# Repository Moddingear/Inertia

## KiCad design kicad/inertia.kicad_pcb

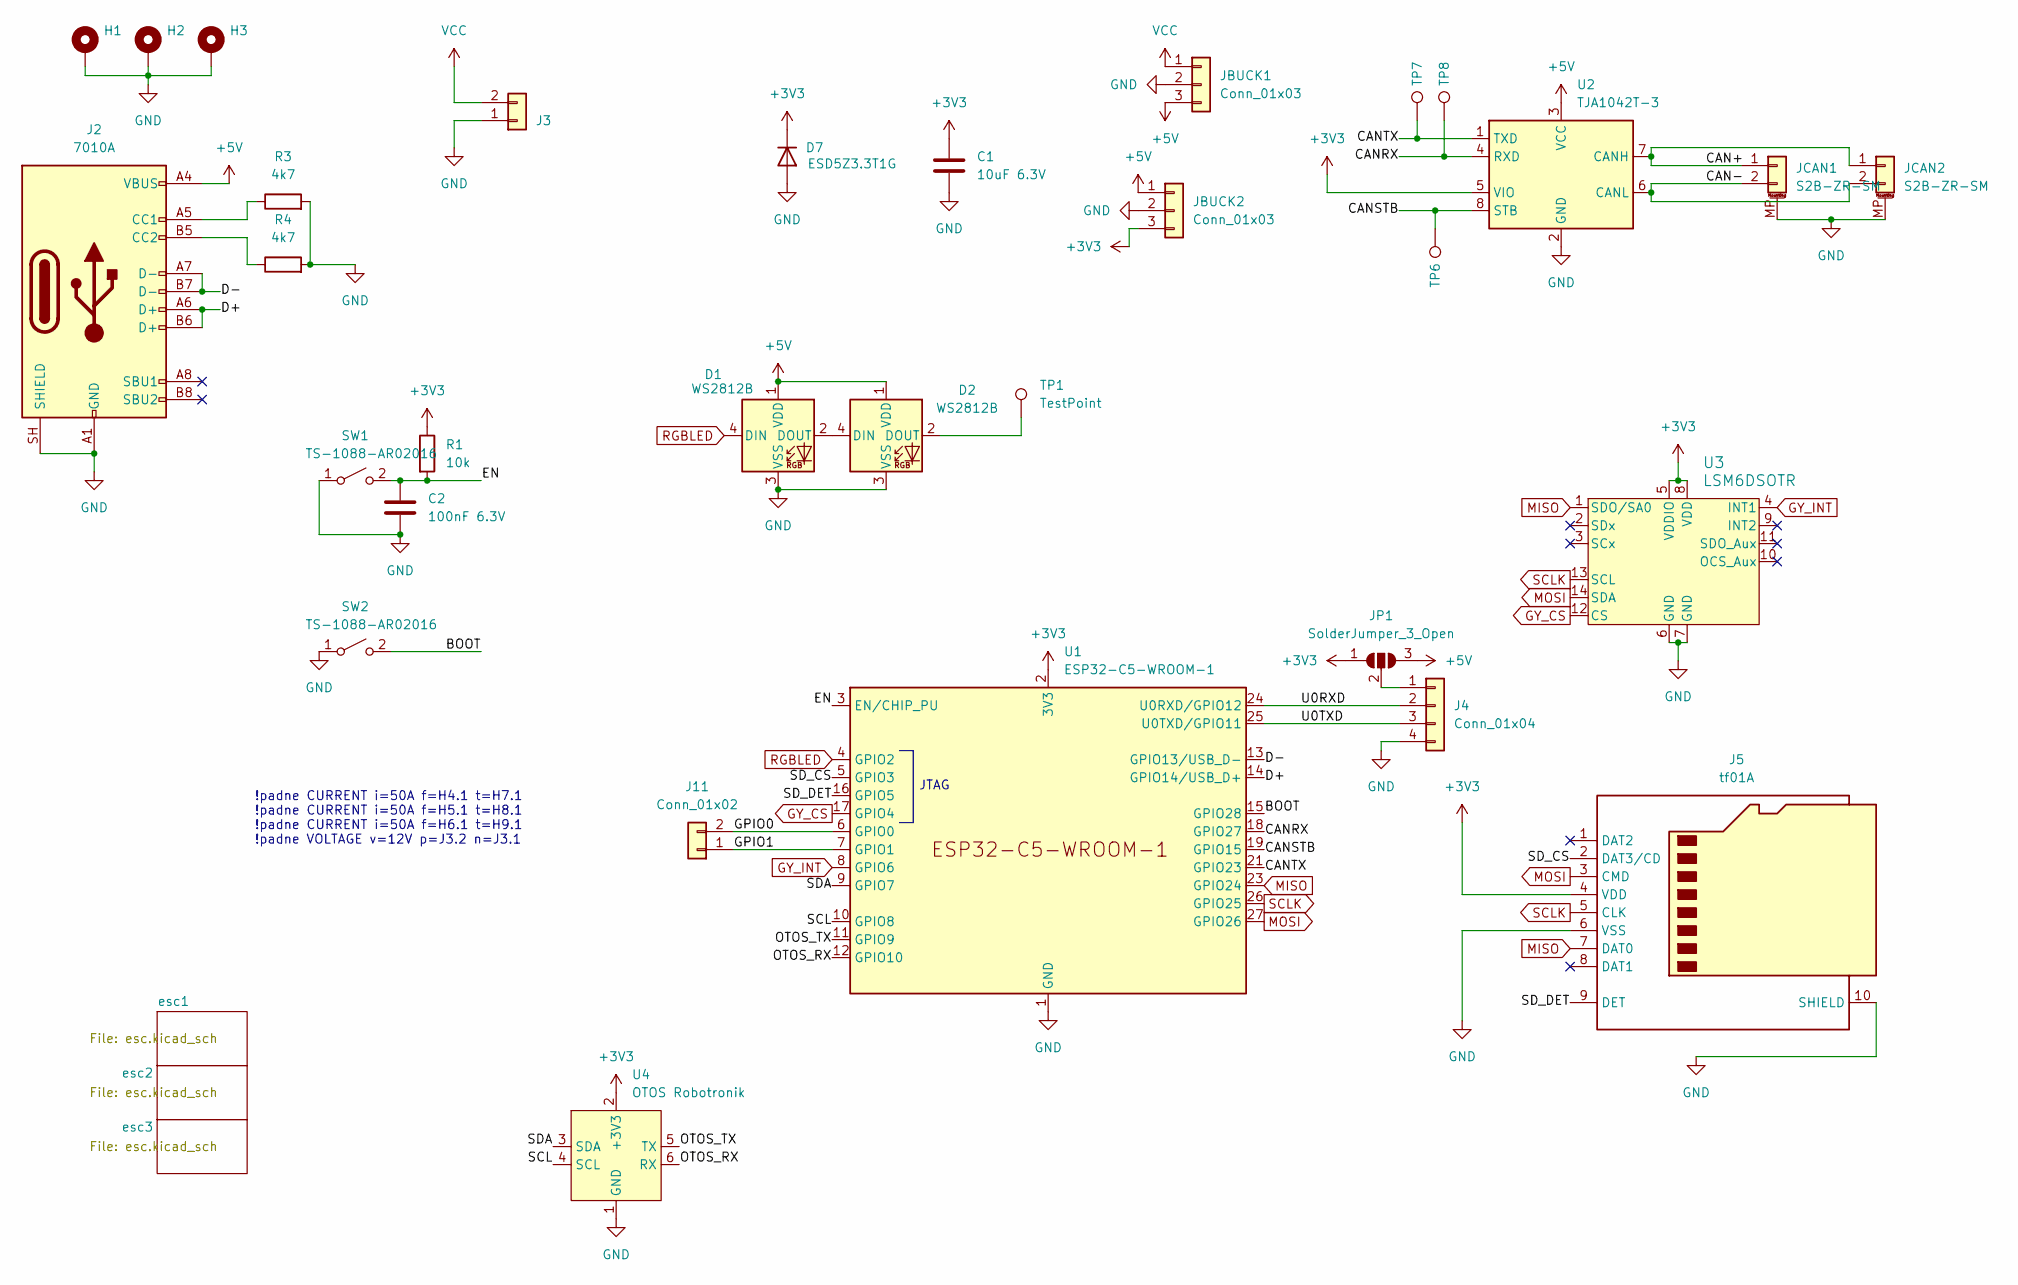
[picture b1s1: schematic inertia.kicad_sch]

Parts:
C1: 10uF 6.3V; C_0805_2012Metric_Pad1.18x1.45mm_HandSolder
C2: 100nF 6.3V; C_0805_2012Metric
D1, D2: WS2812B; LED_WS2812B_PLCC4_5.0x5.0mm_P3.2mm
D7: ESD5Z3.3T1G; D_SOD-523
H1, H2, H3: MountingHole_Pad; MountingHole_3.2mm_M3_ISO7380_Pad
J2: 7010A; USB_C_Receptacle_G-Switch_GT-USB-7010ASV
J3: Conn_01x02; AMASS_XT60-F_1x02_P7.20mm_Vertical
J4: Conn_01x04; JST_XH_B4B-XH-AM_1x04_P2.50mm_Vertical
J5: tf01A; TF-01A
J11: Conn_01x02; JST_XH_B2B-XH-A_1x02_P2.50mm_Vertical
JBUCK1, JBUCK2: Conn_01x03; PinHeader_1x03_P2.54mm_Vertical
JCAN1, JCAN2: S2B-ZR-SM; S2B-ZR-SMxA
JP1: SolderJumper_3_Open; SolderJumper-3_P1.3mm_Open_RoundedPad1.0x1.5mm
R1: 10k; R_0603_1608Metric_Pad0.98x0.95mm_HandSolder
R3, R4: 4k7; R_0603_1608Metric_Pad0.98x0.95mm_HandSolder
SW1, SW2: TS-1088-AR02016; SW_SPST_TS-1088-xR020
TP1: TestPoint; PinHeader_1x01_P2.54mm_Vertical
TP6, TP7, TP8: TestPoint; TestPoint_Pad_D1.0mm
U1: ESP32-C5-WROOM-1
U2: TJA1042T-3; SOIC-8_3.9x4.9mm_P1.27mm
U3: LSM6DSOTR; LGA-14L_2P5X3X0P86_STM
U4: OTOS Robotronik; OTOS_robotronik

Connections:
+3V3: C1.1, D7.1 (K), J5.4 (VDD), JBUCK2.3, JP1.1 (A), R1.1, U1.2 (3V3), U2.5 (VIO), U3.5 (VDDIO), U3.8 (VDD), U4.2 (+3V3)
+5V: D1.1 (VDD), D2.1 (VDD), J2.A4 (VBUS), J2.A9 (VBUS), J2.B4 (VBUS), J2.B9 (VBUS), JBUCK1.3, JBUCK2.1, JP1.3 (B), U2.3 (VCC)
/BOOT: SW2.2 (B), U1.15 (GPIO28)
/CAN+: JCAN1.1, JCAN2.1, U2.7 (CANH)
/CAN-: JCAN1.2, JCAN2.2, U2.6 (CANL)
/CANRX: TP8.1 (1_1), U1.18 (GPIO27), U2.4 (RXD)
/CANSTB: TP6.1 (1_1), U1.19 (GPIO15), U2.8 (STB)
/CANTX: TP7.1 (1_1), U1.21 (GPIO23), U2.1 (TXD)
/D+: J2.A6 (D+), J2.B6 (D+), U1.14 (GPIO14/USB_D+)
/D-: J2.A7 (D-), J2.B7 (D-), U1.13 (GPIO13/USB_D-)
/EN: C2.1, R1.2, SW1.2 (B), U1.3 (EN/CHIP_PU)
/GPIO0: J11.2, U1.6 (GPIO0)
/GPIO1: J11.1, U1.7 (GPIO1)
/OTOS_RX: U1.12 (GPIO10), U4.6 (RX)
/OTOS_TX: U1.11 (GPIO9), U4.5 (TX)
/SCL: U1.10 (GPIO8), U4.4 (SCL)
/SDA: U1.9 (GPIO7), U4.3 (SDA)
/SD_CS: J5.2 (DAT3/CD), U1.5 (GPIO3)
/SD_DET: J5.9 (DET), U1.16 (GPIO5)
/U0RXD: J4.2, U1.24 (U0RXD/GPIO12)
/U0TXD: J4.3, U1.25 (U0TXD/GPIO11)
GND: C1.2, C2.2, D1.3 (VSS), D2.3 (VSS), D7.2 (A), H1.1 (1_1), H2.1 (1_1), H3.1 (1_1), J2.A1 (GND), J2.A12 (GND), J2.B1 (GND), J2.B12 (GND), J2.SH (SHIELD), J3.1, J4.4, J5.6 (VSS), J5.10 (SHIELD), JBUCK1.2, JBUCK2.2, JCAN1.MP (MountPin), JCAN2.MP (MountPin), R3.2, R4.2, SW1.1 (A), SW2.1 (A), U1.1 (GND), U1.28 (GND), U1.29 (GND), U2.2 (GND), U3.6 (GND), U3.7 (GND), U4.1 (GND); also elsewhere on the board
GY_CS: U1.17 (GPIO4), U3.12 (CS)
GY_INT: U1.8 (GPIO6), U3.4 (INT1)
MISO: J5.7 (DAT0), U1.23 (GPIO24), U3.1 (SDO/SA0)
MOSI: J5.3 (CMD), U1.27 (GPIO26), U3.14 (SDA)
unnamed: D1.2 (DOUT), D2.4 (DIN)
unnamed: D2.2 (DOUT), TP1.1 (1_1)
unnamed: J2.A5 (CC1), R3.1
unnamed: J2.B5 (CC2), R4.1
unnamed: J4.1, JP1.2 (C)
RGBLED: D1.4 (DIN), U1.4 (GPIO2)
SCLK: J5.5 (CLK), U1.26 (GPIO25), U3.13 (SCL)
VCC: J3.2, JBUCK1.1; also elsewhere on the board

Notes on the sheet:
!padne CURRENT i=50A f=H4.1 t=H7.1 !padne CURRENT i=50A f=H5.1 t=H8.1 !padne CURRENT i=50A f=H6.1 t=H9.1 !padne VOLTAGE v=12V p=J3.2 n=J3.1
JTAG

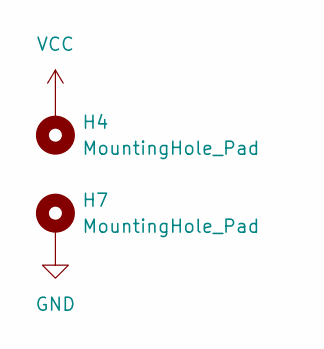
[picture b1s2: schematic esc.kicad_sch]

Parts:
H4, H7: MountingHole_Pad; SMTSOM340

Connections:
GND: H7.1 (1_1); also elsewhere on the board
VCC: H4.1 (1_1); also elsewhere on the board

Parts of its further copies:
H5, H6, H8, H9: MountingHole_Pad; SMTSOM340

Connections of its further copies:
GND: H8.1 (1_1), H9.1 (1_1); also elsewhere on the board
VCC: H5.1 (1_1), H6.1 (1_1); also elsewhere on the board

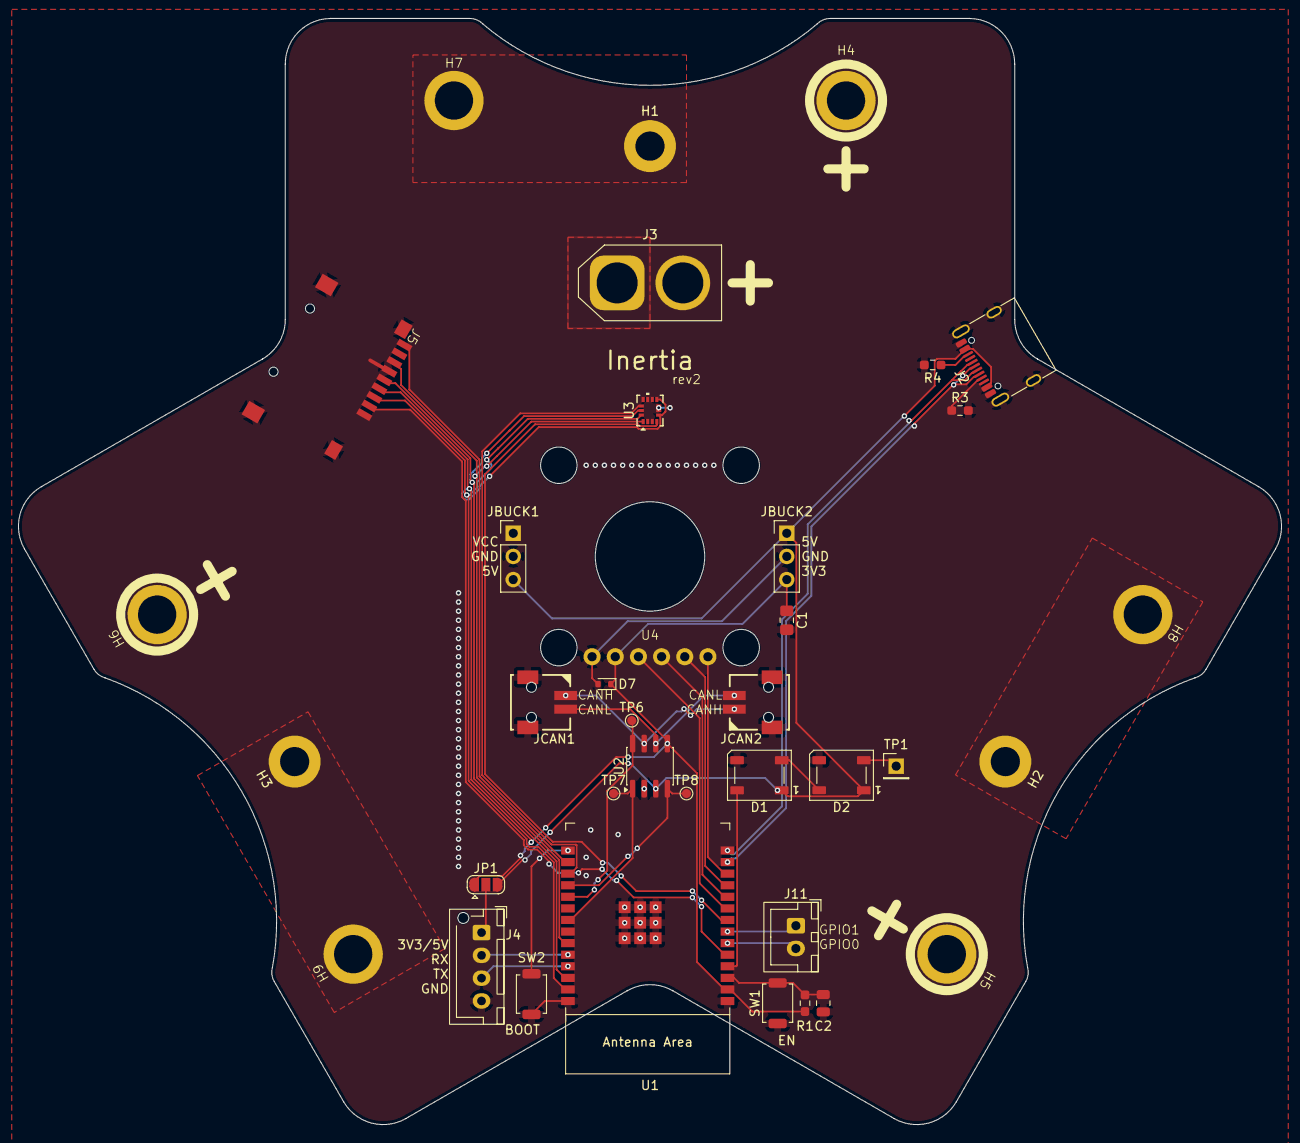
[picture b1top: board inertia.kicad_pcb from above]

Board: 2 copper layers, 138.5 x 121.3 mm, 37 parts (0 on the bottom side), 34 nets.
